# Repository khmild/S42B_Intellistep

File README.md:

# Intellistep

A rework of the terribly coded firmware from the BTT S42B v2 boards.

I am currently working on redoing a lot of the functions found in the firmware. A list of the current things that are being worked on is in the Projects tab. If you don't see your issue there, then please let me know.

***Note: This is a pre-release firmware still in beta testing. It is not ready for actual use yet. Only flash it if you would like to help with the development process. If you compile Intellistep and don't like it, you can always switch back to the production firmware using the file in the "precompiled" folder. The production firmware is `v2ProductionFirmware.bin`. Original BTT build of this project is `firmware-v2.0.bin`***

***Note: For the time being, all serial and CAN messages should start with "<" and end with ">". The serial baud rate is 115200.***

***Note: If you're having large oscillations in step correction, then try increasing the microstepping using the dip switches while increasing the microstep multiplier***

New Features:

- Redone stepping for higher torque and quieter operation
- Redone serial commands (based on gcode)
- Temperature readout on the display
- Motor and driver overtemp current reduction
- Much faster stepper calibration

Future Features:

- CAN subnetwork for driver configuration
- Dynamic current control based on speed and acceleration
- Manual tuning utility for manual PID tuning
- New menu items for setting PID parameters

G/M Code Table

- G6 (ex G6 D0 R1000 S1000) - Direct stepping, commands the motor to move a specified number of steps in the specified direction. D is direction (0 for CCW, 1 for CW), R is rate (in Hz), and S is the count of steps to move. Requires `ENABLE_DIRECT_STEPPING`
- M17 (ex M17) - Enables the motor (overrides enable pin)
- M18 / M84 (ex M18 or M84) - Disables the motor (overrides enable pin)
- M93 (ex M93 V1.8 or M93) - Sets the angle of a full step. This value should be 1.8° or 0.9°. If no value is provided, then the current value will be returned.
- M115 (ex M115) - Prints out firmware information, consisting of the version and any enabled features.
- M116 (ex M116 S1 M"A message") - Simple forward command that will forward a message across the CAN bus. Can be used for pinging or allowing a Serial to connect to the CAN network. Requires `ENABLE_CAN`
- M154 (ex M154 S8) - Runs the manual PID tuning interface. Serial is filled with encoder angles. S parameter specifies update interval in seconds. Requires `ENABLE_PID`
- M301 (ex M301 P1 I1 D1 W10 or M301) - Sets or gets the PID values for the motor. W term is the maximum value of the I windup. If no values are provided, then the current values will be returned. Requires `ENABLE_PID`
- M303 (ex M303) - Runs an autotune sequence for the PID loop. Requires `ENABLE_PID`
- M350 (ex M350 V16 or M350) - Sets or gets the microstepping divisor for the motor. This value can be 1, 2, 4, 8, 16, or 32. If no value is provided, then the current microstepping divisor will be returned.
- M352 (ex M352 S1 or M352) - Sets or gets the direction pin inversion for the motor (0 is standard, 1 is inverted). If no value is provided, then the current value will be returned.
- M353 (ex M353 S1 or M353) - Sets or gets the enable pin inversion for the motor (0 is standard, 1 is inverted). If no value is provided, then the current value will be returned.
- M354 (ex M354 S1 or M354) - Sets or gets if the motor dip switches were installed incorrectly (reversed) (0 is standard, 1 is inverted). If no value is provided, then the current value will be returned.
- M355 (ex M355 V1.34 or M355) - Sets or gets the microstep multiplier for the board. Allows to use multiple motors connected to the same mainboard pin, yet have different rates. If no value is provided, then the current value will be returned. Requires `ENABLE_CAN`
- M356 (ex M356 V1 or M356 VX2 or M356) - Sets or gets the CAN ID of the board. Can be set using the axis character or actual ID. If no value is provided, then the current value will be returned. Requires `ENABLE_CAN`
- M500 (ex M500) - Saves the currently loaded parameters into flash
- M501 (ex M501) - Loads all saved parameters from flash
- M502 (ex M502) - Wipes all parameters from flash, then reboots the system
- M907 (ex M907 R750, M907 I500) - Sets or gets the RMS(R) or Peak(P) current in mA. If dynamic current is enabled, then the accel(A), idle(I), and/or max(M) can be set or retrieved. If no value is set, then the current RMS current (not dynamic current) or the accel, idle, and max terms (dynamic current) will be returned.

Using dip switches
| Dip switch mappings
| PIN     |    Normal orientation      |  Reversed orientation |
|---------|----------------------------|-----------------------|
| DIP_1   |    Microstep 1             |  Calibration mode     |
| DIP_2   |    Microstep 2             |  Closed/Open loop     |
| DIP_3   |    Closed/Open loop        |  Microstep 2          |
| DIP_4   |    Calibration mode        |  Microstep 1          |

## Authors

## Credits

- [BTT](https://github.com/bigtreetech) - [Original code](https://github.com/bigtreetech/BIGTREETECH-Stepper-Motor-Driver)
- [CAP1Sup](https://github.com/CAP1Sup) - Main rewrite of code
- [IhorNehrutsa](https://github.com/IhorNehrutsa) - Large performance gains, general code work
- [TazerReloaded](https://github.com/TazerReloaded) - Encoder protocol and communication, much faster snprintf string printing
- [jlmxyz](https://github.com/jlmxyz) - Board schematics (in KiCad folder)
- [Misfittech](https://github.com/Misfittech) - The [Smart Stepper project](https://github.com/Misfittech/nano_stepper). This was a large help when writing the correct stepping code.
- [Matt Fryer](https://github.com/MattFryer) - [Smoothed](https://github.com/MattFryer/Smoothed) library. This was a huge help when smoothing out the OLED values to make them more readable and accurate
- [Marlin](https://github.com/MarlinFirmware/Marlin) - Autobuilding templates

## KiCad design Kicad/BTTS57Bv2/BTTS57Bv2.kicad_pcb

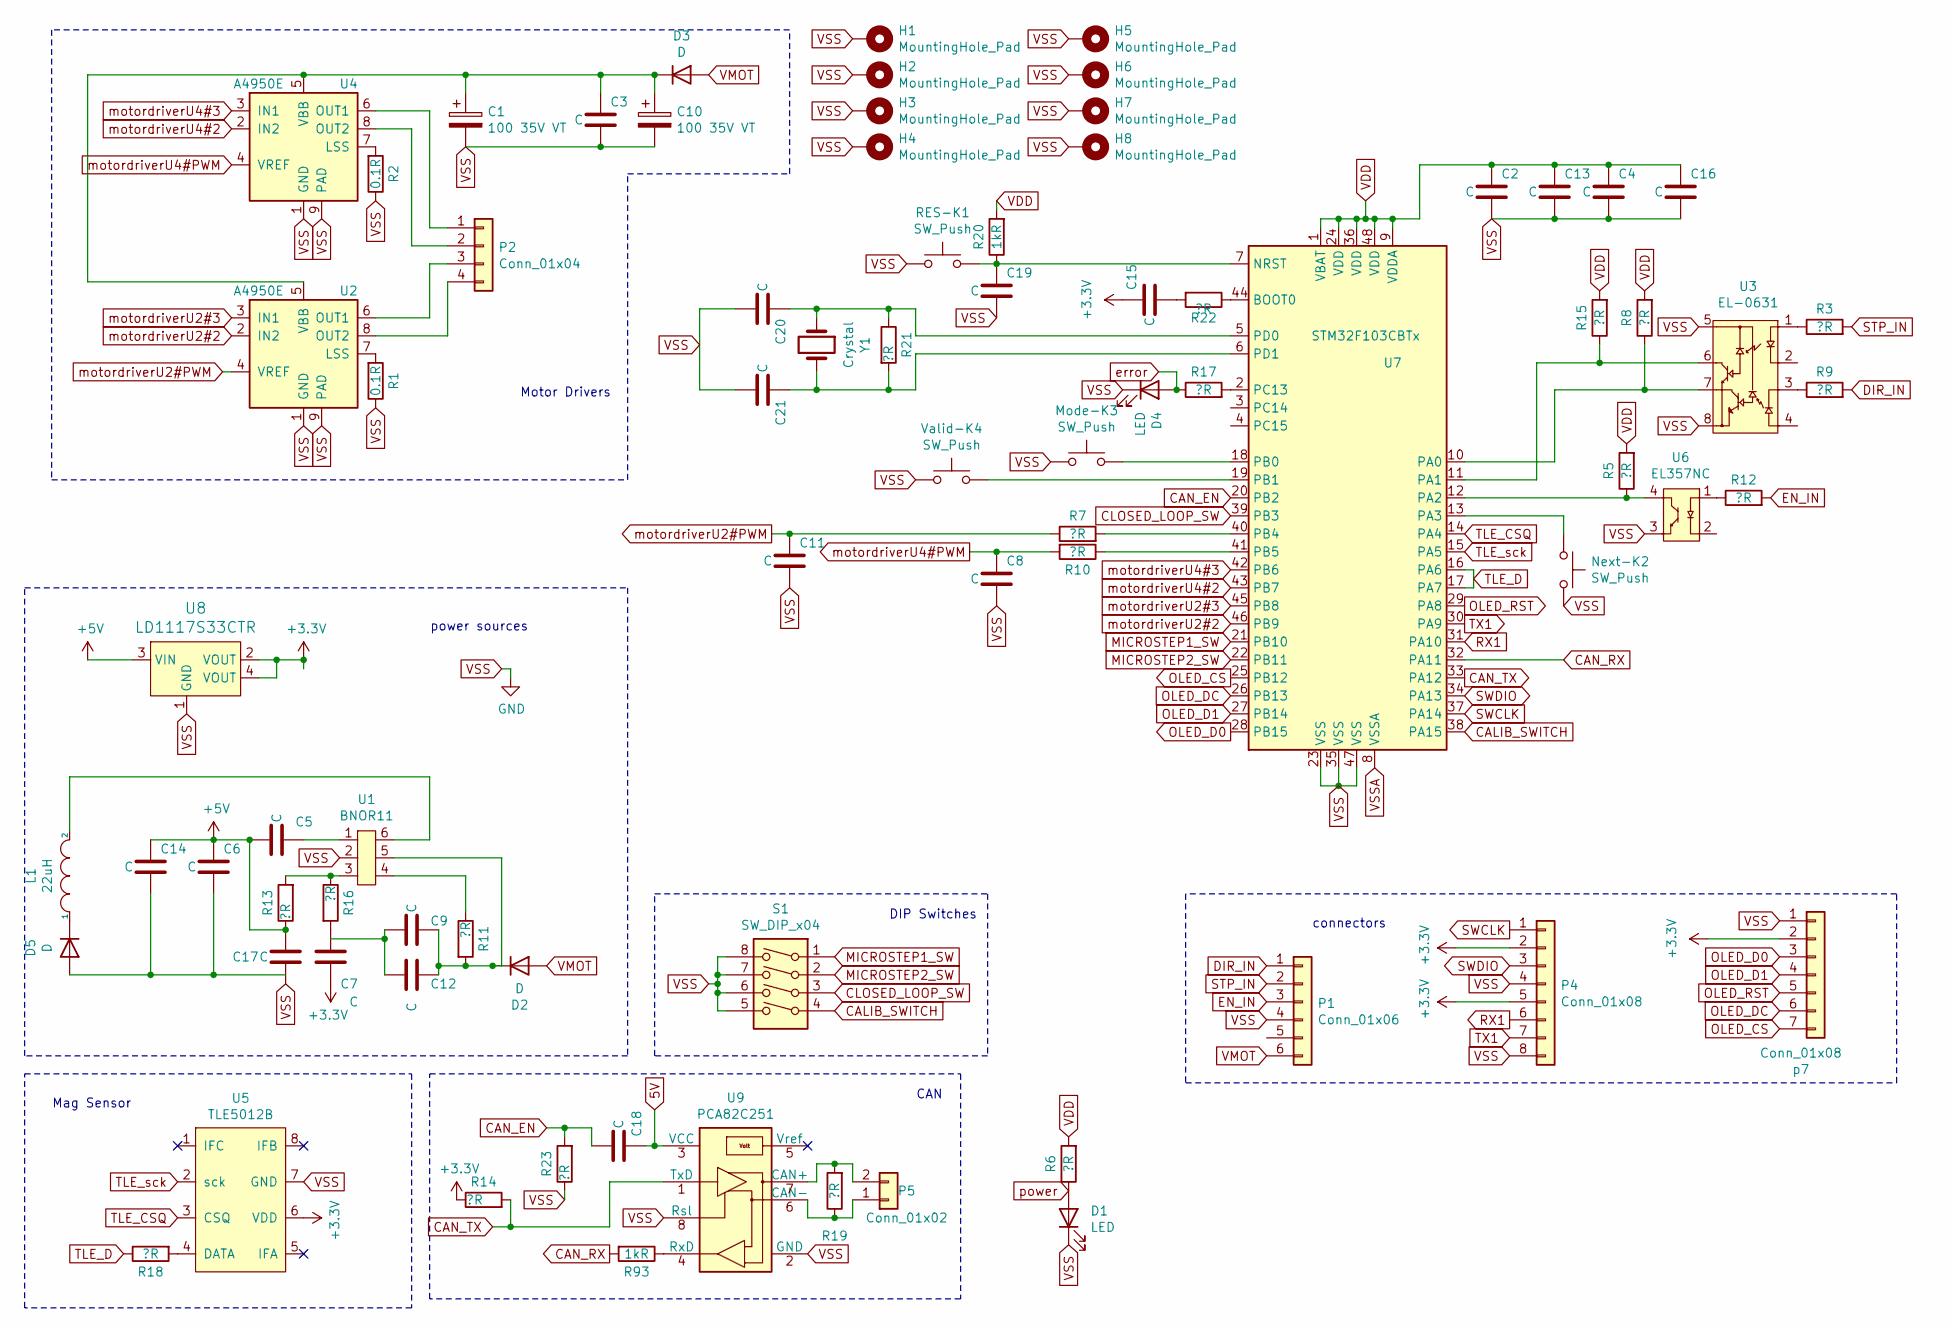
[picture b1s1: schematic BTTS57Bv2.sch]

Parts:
C1, C10: 100 35V VT; CP_Elec_6.3x7.7
C2, C4, C5, C8, C11, C12, C13, C14, C15, C16, C18, C19, C20, C21: C; C_0603_1608Metric
C3, C7, C17: C; C_1812_4532Metric
C6, C9: C; C_0805_2012Metric
D1, D4: LED; LED_0603_1608Metric
D2, D3, D5: D; D_2512_6332Metric
H1, H2, H3, H4, H5, H6, H7, H8: MountingHole_Pad; MountingHole_2.7mm_M2.5_ISO14580_Pad_TopBottom
L1: 22uH; L_Wuerth_MAPI-4030
Mode-K3: SW_Push; SW_Push_1P1T-SH_NO_CK_KMR2xxG
Next-K2: SW_Push; SW_Push_1P1T-SH_NO_CK_KMR2xxG
P1: Conn_01x06; JST_XH_B6B-XH-A_1x06_P2.50mm_Vertical
P2: Conn_01x04; JST_XH_B4B-XH-A_1x04_P2.50mm_Vertical
P4: Conn_01x08; PinHeader_1x08_P2.54mm_Vertical
P5: Conn_01x02; JST_XH_B2B-XH-AM_1x02_P2.50mm_Vertical
R1, R2: 0.1R; R_2512_6332Metric
R3, R9, R12, R18: ?R; R_0805_2012Metric
R5, R6, R7, R8, R10, R11, R13, R14, R15, R16, R17, R21, R22, R23: ?R; R_0603_1608Metric
R19: ?R; R_1206_3216Metric
R20, R93: 1kR; R_0603_1608Metric
RES-K1: SW_Push; SW_Push_1P1T-SH_NO_CK_KMR2xxG
S1: SW_DIP_x04; SW_DIP_SPSTx04_Slide_KingTek_DSHP04TS_W7.62mm_P1.27mm
U1: BNOR11
U2, U4: A4950E; SOIC-8-1EP_3.9x4.9mm_P1.27mm_EP2.41x3.3mm
U3: EL-0631; SOP-8_3.9x4.9mm_P1.27mm
U5: TLE5012B
U6: EL357NC; SOP-4_3.8x4.1mm_P2.54mm
U7: STM32F103CBTx; LQFP-48_7x7mm_P0.5mm
U8: LD1117S33CTR; SOT-223; MPN LD1117S33CTR; Digi-Key_PN 497-1241-1-ND
U9: PCA82C251; SO-8_3.9x4.9mm_P1.27mm
Valid-K4: SW_Push; SW_Push_1P1T-SH_NO_CK_KMR2xxG
Y1: Crystal
p7: Conn_01x08; PinSocket_1x07_P2.54mm_Vertical

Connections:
5V: C18.1, U9.3 (VCC)
+3V3: C7.2, C15.1, P4.2, P4.5, R14.1, U5.6 (VDD), U8.2 (VOUT), U8.4 (VOUT), p7.2
+5V: C5.2, C6.1, C14.1, C17.1, R13.1, U8.3 (VIN)
CALIB_SWITCH: S1.4, U7.38 (PA15)
CAN_EN: C18.2, R23.2, U7.20 (PB2)
CAN_RX: R93.2, U7.32 (PA11)
CAN_TX: R14.2, U7.33 (PA12), U9.1 (TxD)
CLOSED_LOOP_SW: S1.3, U7.39 (PB3)
DIR_IN: P1.1, R9.2
EN_IN: P1.3, R12.2
MICROSTEP1_SW: S1.1, U7.21 (PB10)
MICROSTEP2_SW: S1.2, U7.22 (PB11)
unnamed: C1.1, C3.1, C10.1, D3.1 (K), U2.5 (VBB), U4.5 (VBB)
unnamed: C5.1, U1.1
unnamed: C7.1, R16.2
unnamed: C9.1, C12.1, D2.1 (K), R11.2, U1.5
unnamed: C9.2, C12.2
unnamed: C6.2, C14.2, D5.2 (A)
unnamed: C15.2, R22.2
unnamed: C19.1, R20.1, RES-K1.2, U7.7 (NRST)
unnamed: C20.1, R21.1, U7.5 (PD0), Y1.1
unnamed: C21.1, R21.2, U7.6 (PD1), Y1.2
unnamed: D5.1 (K), L1.1
unnamed: L1.2, U1.6
unnamed: Mode-K3.2, U7.18 (PB0)
unnamed: Next-K2.1, U7.13 (PA3)
unnamed: P2.1, U4.6 (OUT1)
unnamed: P2.2, U4.8 (OUT2)
unnamed: P2.3, U2.6 (OUT1)
unnamed: P2.4, U2.8 (OUT2)
unnamed: P5.1, R19.1, U9.6 (CAN-)
unnamed: P5.2, R19.2, U9.7 (CAN+)
unnamed: R1.2, U2.7 (LSS)
unnamed: R2.2, U4.7 (LSS)
unnamed: R3.1, U3.1
unnamed: R5.1, U6.4, U7.12 (PA2)
unnamed: R7.2, U7.40 (PB4)
unnamed: R8.1, U3.7, U7.10 (PA0)
unnamed: R9.1, U3.3
unnamed: R10.1, U7.41 (PB5)
unnamed: R11.1, U1.4
unnamed: R12.1, U6.1
unnamed: R13.2, R16.1, U1.3
unnamed: R15.1, U3.6, U7.11 (PA1)
unnamed: R17.2, U7.2 (PC13)
unnamed: R18.2, U5.4 (DATA)
unnamed: R22.1, U7.44 (BOOT0)
unnamed: R93.1, U9.4 (RxD)
unnamed: U7.19 (PB1), Valid-K4.2
OLED_CS: U7.25 (PB12), p7.7
OLED_D0: U7.28 (PB15), p7.3
OLED_D1: U7.27 (PB14), p7.4
OLED_DC: U7.26 (PB13), p7.6
OLED_RST: U7.29 (PA8), p7.5
RX1: P4.6, U7.31 (PA10)
STP_IN: P1.2, R3.2
SWCLK: P4.1, U7.37 (PA14)
SWDIO: P4.3, U7.34 (PA13)
TLE_CSQ: U5.3 (CSQ), U7.14 (PA4)
TLE_D: R18.1, U7.16 (PA6), U7.17 (PA7)
TLE_sck: U5.2 (sck), U7.15 (PA5)
TX1: P4.7, U7.30 (PA9)
VDD: C2.1, C4.1, C13.1, C16.1, R5.2, R6.2, R8.2, R15.2, R20.2, U7.1 (VBAT), U7.9 (VDDA), U7.24 (VDD), U7.36 (VDD), U7.48 (VDD)
VMOT: D2.2 (A), D3.2 (A), P1.6
VSS: C1.2, C2.2, C3.2, C4.2, C8.2, C10.2, C11.2, C13.2, C16.2, C17.2, C19.2, C20.2, C21.2, D1.1 (K), D4.1 (K), H1.1, H2.1, H3.1, H4.1, H5.1, H6.1, H7.1, H8.1, Mode-K3.1, Next-K2.2, P1.4, P4.4, P4.8, R1.1, R2.1, R23.1, RES-K1.1, S1.5, S1.6, S1.7, S1.8, U1.2, U2.1 (GND), U2.9 (PAD), U3.5, U3.8, U4.1 (GND), U4.9 (PAD), U5.7 (GND), U6.3, U7.23 (VSS), U7.35 (VSS), U7.47 (VSS), U8.1 (GND), U9.2 (GND), U9.8 (Rsl), Valid-K4.1, p7.1
VSSA: U7.8 (VSSA)
error: D4.2 (A), R17.1
motordriverU2#2: U2.2 (IN2), U7.46 (PB9)
motordriverU2#3: U2.3 (IN1), U7.45 (PB8)
motordriverU2#PWM: C11.1, R7.1, U2.4 (VREF)
motordriverU4#2: U4.2 (IN2), U7.43 (PB7)
motordriverU4#3: U4.3 (IN1), U7.42 (PB6)
motordriverU4#PWM: C8.1, R10.2, U4.4 (VREF)
power: D1.2 (A), R6.1

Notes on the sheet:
power sources
Mag Sensor
CAN
DIP Switches
connectors
Motor Drivers

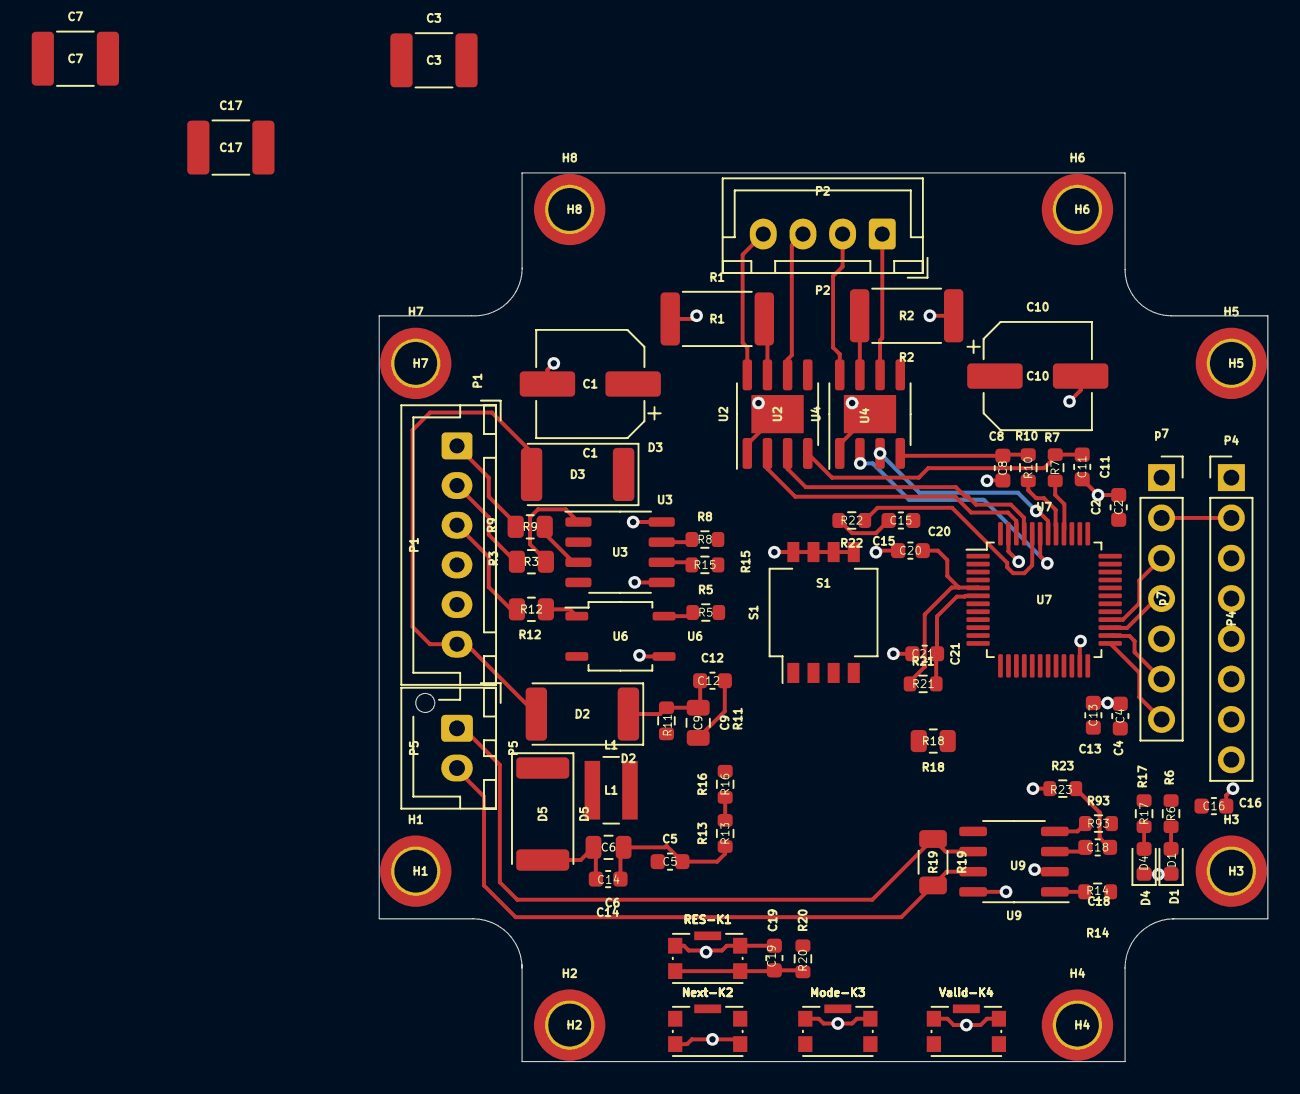
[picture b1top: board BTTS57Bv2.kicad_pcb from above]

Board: 2 copper layers, 56.0 x 56.0 mm, 74 parts (0 on the bottom side), 67 nets.

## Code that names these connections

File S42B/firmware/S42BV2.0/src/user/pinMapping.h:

#ifndef __PINMAPPING_H
#define __PINMAPPING_H

/*
// * = F103C8-CB    | DIGITAL | ANALOG | USART      | TWI       | SPI        | SPECIAL   |
//                  |---------|--------|------------|-----------|------------|-----------|
#define PA0  A0  // | 0       | A0     |            |           |            |           |
#define PA1  A1  // | 1       | A1     |            |           |            |           |
#define PA2  A2  // | 2       | A2     | USART2_TX  |           |            |           |
#define PA3  A3  // | 2       | A2     | USART2_RX  |           |            |           |
#define PA4  A4  // | 4       | A4     |            |           | SPI1_SS    |           |
#define PA5  A5  // | 5       | A5     |            |           | SPI1_SCK   |           |
#define PA6  A6  // | 6       | A6     |            |           | SPI1_MISO  |           |
#define PA7  A7  // | 7       | A7     |            |           | SPI1_MOSI  |           |
#define PA8  8   // | 8       |        |            |           |            |           |
#define PA9  9   // | 9       |        | USART1_TX  |           |            |           |
#define PA10 10  // | 10      |        | USART1_RX  |           |            |           |
#define PA11 11  // | 11      |        |            |           |            | USB_DN    |
#define PA12 12  // | 12      |        |            |           |            | USB_DP    |
#define PA13 13  // | 13      |        |            |           |            | SWD_SWDIO |
#define PA14 14  // | 14      |        |            |           |            | SWD_SWCLK |
#define PA15 15  // | 15      |        |            |           | SPI1_SS    |           |
//                  |---------|--------|------------|-----------|------------|-----------|
#define PB0  A8  // | 16      | A8     |            |           |            |           |
#define PB1  A9  // | 17      | A9     |            |           |            |           |
#define PB2  18  // | 18      |        |            |           |            | BOOT1     |
#define PB3  19  // | 19      |        |            |           | SPI1_SCK   |           |
#define PB4  20  // | 20      |        |            |           | SPI1_MISO  |           |
#define PB5  21  // | 21      |        |            |           | SPI1_MOSI  |           |
#define PB6  22  // | 22      |        | USART1_TX  | TWI1_SCL  |            |           |
#define PB7  23  // | 23      |        | USART1_RX  | TWI1_SDA  |            |           |
#define PB8  24  // | 24      |        |            | TWI1_SCL  |            |           |
#define PB9  25  // | 25      |        |            | TWI1_SDA  |            |           |
#define PB10 26  // | 26      |        | USART3_TX* | TWI2_SCL* |            |           |
#define PB11 27  // | 27      |        | USART3_RX* | TWI2_SDA* |            |           |
#define PB12 28  // | 28      |        |            |           | SPI2_SS*   |           |
#define PB13 29  // | 29      |        |            |           | SPI2_SCK*  |           |
#define PB14 30  // | 30      |        |            |           | SPI2_MISO* |           |
#define PB15 31  // | 31      |        |            |           | SPI2_MOSI* |           |
//                  |---------|--------|------------|-----------|------------|-----------|
#define PC13 32  // | 32      |        |            |           |            |           |
#define PC14 33  // | 33      |        |            |           |            | OSC32_IN  |
#define PC15 34  // | 34      |        |            |           |            | OSC32_OUT |
//                  |---------|--------|------------|-----------|------------|-----------|
#define PD0  35  // | 35      |        |            |           |            | OSC_IN    |
#define PD1  36  // | 36      |        |            |           |            | OSC_OUT   |
//                  |---------|--------|------------|-----------|------------|-----------|
*/

// OLED Mappings
#define OLED_CS_PIN   PB12
#define OLED_RST_PIN  PA8
#define OLED_SCLK_PIN PB13
#define OLED_SDIN_PIN PB14 // D1
#define OLED_DC_PIN   PB15 // ! Needs checked!
#define OLED_CS_GPIO_PORT  GPIOB
#define OLED_RST_GPIO_PORT GPIOB
#define OLED_DC_GPIO_PORT  GPIOB

// Button mappings
#define DOWN_BUTTON_PIN         PA3
#define BACK_BUTTON_PIN         PB0
#define SELECT_BUTTON_PIN       PB1

// Dip switch mappings
#define DIP_CALIBRATED          PA15
#define DIP_CLOSED_LOOP         PB3
#define DIP_MICRO_1             PB10
#define DIP_MICRO_2             PB11

// LED pin
#define LED_PIN PC13

// Motor mappings
#define COIL_A_DIR_1        PB6
#define COIL_A_DIR_2        PB7
#define COIL_B_DIR_1        PB8
#define COIL_B_DIR_2        PB9
#define COIL_A_POWER_OUTPUT PB4
#define COIL_B_POWER_OUTPUT PB5

// Encoder SPI interface
#define ENCODER_SS   PA4 // SPI1_SS
#define ENCODER_SCK  PA5 // SPI1_SCK
#define ENCODER_MISO PA6 // SPI1_MISO
#define ENCODER_MOSI PA7 // SPI1_MOSI

// Stepping interface
#define STEP_PIN      PA1 // ! according to the previous files, but this is the same as the dir pin
#define ENABLE_PIN    PA2
#define DIRECTION_PIN PA1

// CAN bus pins
#define CAN_IN_PIN  PA11
#define CAN_OUT_PIN PA12



// Options
#define CLOSED_LOOP
#define CLOSED_LOOP_CONFIG
//#define TEST_FLASH
#define STEPPER_UPDATE_FREQ 10

// Encoder speed estimation instead of actual value (saves memory)
//#define ENCODER_ESTIMATION

// Motor constants
#define STEP_ANGLE 1.8 // ! Check to see for .9 deg motors as well
#define MAX_CURRENT 3500 // Maximum current in mA
#define MAX_MICROSTEP_DIVISOR 32 // The maximum microstepping divisor

#endif //__PINMAPPING_H

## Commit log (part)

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2021-02-15 Wrote motor groundwork, reintroduced flash, and continued work on menu display
2021-02-19 Added serial interface (needs parser), added loading saved values
2021-02-21 Fixed some minor issues with the parser
2021-02-23 Added TLE5012 library, needs implementation
2021-02-23 Fixed compilation error
2021-02-23 Added command to save parameters to flash, more parser work
2021-02-24 Added microstepping menu, needs enable and direction menus
2021-02-25 Moved parser to seperate file in prep for CAN reimplementation
2021-02-28 Added hardware timers with IRQ for stepper
2021-02-28 Fixed README and minor stepping speed issue
2021-02-28 Added datasheets for components
2021-03-01 Fixed serial reads
2021-03-01 Updated warning to README and added quick call to parse the serial data
2021-03-01 Updated README with serial baud
2021-03-02 Added debugging print
2021-03-04 Changed motor operation to only use PID for corrections
2021-03-19 Fixed issues with firmware lock (caused by encoder). Menu system is almost fully functional
2021-03-20 Fixed include error from c_cpp_properties.json
2021-03-30 Redid the stepper coil calculations with help from Misfittech. Note that this still needs testing
2021-03-30 Fixed coding issue with motor class and added blank menu item before wraparound
2021-03-31 Added step correction (not enabled, needs encoder yet)
2021-04-03 Added microstep multiplier (request of @maracMB)
2021-04-03 Moved encoder back to library, no values yet
2021-04-05 Bypassed booting issue, added debug print. Encoder still not working
2021-04-06 Fixed logic issues with stepping timers. Needs second lookover
2021-04-06 Redid timers and stepping method. Added StallFault detection.
2021-04-06 Added option to StallFault based on angle deviation
2021-04-08 Moved to manual encoder SPI config. Not working yet
2021-04-09 Roughly fixed delays, tried to fix encoder issue, no luck
2021-04-11 Encoder values are here! Just stepping left. Thanks to TazerReloaded for the fix
2021-04-11 Added speed estimation, fixed temp and angle values
2021-04-11 Fixed readMultipleEncoderRegisters removed some debug statements
2021-04-13 Fixed sine coil calculations, added script to generate table
2021-04-14 Massively improved OLED code and much higher speeds
    OLED code was commented and redone for readability. Screen buffer is written only when needed
2021-04-15 Fixed enabling and current calculations. Stepping still needs work
2021-04-20 OLED cleanup, motor function consolidation, bootscreen
    Also added versioning and gcode for firmware info
2021-04-29 Added feature selection and firmware feature print
2021-04-30 Added exclusion for 0 current for motor.
    Should fix issues with extra current draw.
2021-05-06 Found issue with stepping. Added stepping (only for debugging), disabled CAN
    Issue was caused by CAN bus trying to use the same pins. The CAN library needs a minor rewrite
2021-05-06 Added encoder absolute angle and offset calibration, needs testing
2021-05-07 Added encoder zeroing
2021-05-10 Issues with encoder revolutions should be fixed
    Needs testing. Manually set bits instead of using the TLE library's version
2021-05-10 Still have encoder issues with revolutions, library issues
    Rewrite of library is broken. All of OLED is now cleared after the motor data.
2021-05-11 MovingAverage library fixed, speed gains are evident
2021-05-11 Added OLED renaming, needs testing
2021-05-12 Added autobuilding configs, removed old define
2021-05-12 Fixed filenaming issue with autobuilding
2021-05-13 Fixed minor issues were display was not updating
2021-05-13 Autobuilding should be fixed
2021-05-13 Removed old autobuild file
2021-05-13 Added Marlin credit
2021-05-17 Display warning implementation
2021-05-18 Minor addition to set current to deal with loopback
2021-05-19 Fixed OLED call for speed estimation
2021-05-20 Changed RPM to 2 decimal places
2021-05-20 Improved output for unstable numbers
2021-06-05 reverse engeenering v0.1.0 - need verification : - CAN_EN - double checks all non MCU connected signals - clock generation
2021-06-07 added footprint information changed orientation of oled connector added mounting holes PCB reverse creation (high parts are positionned according measurements, same for outline)
2021-06-09 Fixed 2 minor issues with step correction
2021-06-13 Fixed forced enable issue, began flash rework, added returns to blank commands
    Flash isn't ready yet, but soon. Also fixed issues with correction timer not being reset correctly
2021-06-15 Fixed minor issue causing build to fail with dynamic current
2021-06-16 Fixed minor logic error with stepping IRQ
2021-06-17 Save a little time in fastSin() and fastCos()
    Use SINE_VAL_COUNT as a power of 2.
2021-06-17 Flash works properly now
    Re-enabled calibration check (still doesn't do anything) and added message at boot
2021-06-17 Added M115 support for overtemp and restructured M115 print
2021-06-17 Added OLED parameter saving, loading, and wiping
    Also redid some of the OLED prints to be based on a #defined line height
2021-06-18 Cleanup fastSine.h
2021-06-18 revert
2021-06-20 Added temporary fix for motor calibration issues
    Also fixed unwanted back button behavior on calibration prompt
2021-06-22 Create main_formatted.c
    Save main.c as main_formatted.c and format it in VisualCode
2021-06-23 Revert motor.cpp
2021-06-23 Revert main.cpp
2021-06-23 Fixed issue with SYSCLK selection
2021-06-23 Fixed missed setCoil lines
2021-06-24 StallFault should be working with LED (not tested or enabled)
2021-06-24 Added Klipper files
    Completely unorganized, unworking, and probably going to fail when building
2021-06-24 Add Cube project
2021-06-24 Fixed issues with remaining flash PID references
2021-06-26 Added DS_Store to git ignore
2021-06-28 speedup
2021-06-29 Fixed issues with direction pins not being intialized
2021-06-29 CHECK_GPIO_OUTPUT_SWITCHING
2021-06-29 Fixed motor PWM freq and version number
    In response to https://github.com/CAP1Sup/Intellistep/issues/39
2021-06-30 Update flash.cpp
    Fix #41
2021-06-30 Update main.cpp
    while formatting
2021-06-30 Update timers.cpp
    Add CHECK_STEPPING_RATE funtionality
2021-06-30 Remove unused 'direction' parametr from driveCoils()
2021-06-30 Use separate previousCoilState's for motor coils
2021-06-30 StepperMotor::simpleStep() for tests
2021-06-30 Enable all compiler warnings
2021-06-30 Added parenthesis, modified how steps are calculated
2021-06-30 Cleanup of files, moved all calls to use GPIO_READ
2021-06-30 Added PID warning in preparation to merge with master
2021-07-01 StepperMotor.reversed must be signed type
2021-07-02 SINE_MAX a power of 2 to fast division to SINE_MAX
2021-07-02 Use uint16_t in analogSet() and analogSetup()
2021-07-02 Performance curves of stepper motor on page 2
2021-07-02 Added better notes, minor changes
    SINE_POWER is automatically computed during build, fixed PWM uint16_ts
2021-07-02 Moved SINE_MAX sanity checks to their respective file
2021-07-02 Added note on FALLING step pin
2021-07-05 128MHz overclock
2021-07-06 Measure PLLCLK on MCO(PA8)
2021-07-06 Fixed the previous coil state so that it is set at boot
2021-07-06 Rewrote PID, added tuner project, added I windup limit
    PID should be fully functional.
2021-07-07 Re-enabled the startup offset and moved flash program to IRQ
2021-07-07 Added direct stepping
    Also changed around parser to support DS and added timer
2021-07-07 Fixed missing reference due to encoder class creation
2021-07-08 Reduce motor noise: Set MOTOR_PWM_FREQ to 140kHz
    140kHz measured in origin BTT board.
    See https://github.com/CAP1Sup/Intellistep/issues/39
2021-07-08 Moved PWM settings to config
2021-07-08 Set motor PWM 139.5kHz and 9bit resolution
2021-07-09 Split getAngle() to getAngleNow() and getAngleAvg()
2021-07-09 Check encoder speed
2021-07-09 Remove the LGPL comment as inaccurate
2021-07-09 Init running total to zero
2021-07-09 Reduce code size
2021-07-09 Use integer MovingAverage to encoder Angle funcctions
2021-07-11 First try at DMA transfer, no luck so far
    Transfer complete function doesn't seem to be called
2021-07-12 Serial.setTx() Serial.setRx()
2021-07-12 Code review of Encoder Temperature
2021-07-12 Cleaned up config.h
2021-07-13 Added credit for board schematics
2021-07-13 Replace pow() function to constant macro
2021-07-13 Cleaned up config.h, moved most macros to macros.h
    Should help to keep the config clean for when people configure it
2021-07-13 Fix !ENCODER_SPEED_ESTIMATION
2021-07-14 Hardware step counter
    Steps are also counted by a separate hardware counter, allowing higher precision. Needs over/underflow interrupts
2021-07-14 Minor changes, new debugging section, flash version ignore
    Also cleaned up getRev and made it an integer
2021-07-14 Fix Encoder::getTemp()
2021-07-15 Finished hardware counter
    PID now uses the hardware counter as its reference
2021-07-15 Added enable pin config (accidentally removed)
2021-07-15 Fix microstepMultiplier
2021-07-15 5.6 hour in one direction for counter overflow
2021-07-16 Use momentary values of encoder with rejected LSB
2021-07-17 Clarification and cleanup
    Moved config into separate files, streamlining process for end users
2021-07-17 Renamed encoder function, reorganized configs
    Configs are now in a separate folder, making it easier to keep configs separate from coded files
2021-07-17 Minor conventions cleanup
2021-07-17 Fixed version and minor issue with hardware step count
2021-07-19 Started work on enabling issue, not finished yet
2021-07-19 Use indexPointsMultiplier
2021-07-27 Cleanup of unneeded additions and calculations
    Angles are no longer calculated, they can be found by multipling the current step count by the microstepAngle
2021-07-28 Select only step/dir mode
2021-08-03 Fixes to setState
    Set state should now work properly
2021-08-03 Fixed minor issue with ambigous call
2021-08-04 Remove CLOCKWISE and COUNTER_CLOCKWISE
2021-08-05 Use POSITIVE/NEGATIVE
2021-08-06 Use momentary encoder.getAbsoluteAngle()
2021-08-08 bug fix : wrong pin count order on optical tranceivers
2021-08-10 private microstepMultiplier
2021-08-11 Zero the encoder after the motor is enabled
2021-08-11 delay(500)
2021-08-13 Fix software counter direction
2021-08-13 Merge remote-tracking branch 'origin/dev' into RevIngSchematics
    # Conflicts:
    # .gitignore
    # Kicad/BTTS42Bv2/BTTS42Bv2-cache.lib
    # Kicad/BTTS42Bv2/BTTS42Bv2.sch
    # Kicad/BTTS42Bv2/BTT_S57B_v2.0_reverseIng.0.1.1.pdf
2021-08-13 renaming folder name
2021-08-14 Set priority groupping explicitly to 3.1(PRIO.SUBPRIO)
2021-09-02 Fixed issues with saving that cause encoder output to be "nan"
    Should fix https://github.com/CAP1Sup/Intellistep/issues/107
2021-11-21 Hardware counting improvements
    Motor setup now uses STM library. Minor miscounting does occasionally occur, causing drifts of around 1-2 steps, but these occur rarely. More work needs done yet. Also added feature to display step c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
2021-11-27 Minor commenting adjustment, makes objective clearer
2021-11-28 Added optimized function for much faster GPIO7 writes
    Improves encoder read and write speeds. Also fixed version number
2021-11-29 Added legacy step code and option to switch between
    Another attempt at #111. No luck still
2021-12-02 Added nice cycling animation to calibration messages
2021-12-10 Added enable pin interrupt support
    This is disabled as the functionality is untested
2021-12-10 Added preprocessor statement to scrolling logic
    Fixes extra unnecessary variables when OLED isn't enabled
2021-12-11 Fixed motor not disabling (PULLDOWN -> PULLUP)
2021-12-12 Added MKS step counting. Original encoder setup better
2022-01-29 Default to no overclock, flash load optimization
2022-01-29 Minor adjustment to README
2022-02-08 Adjusted warning message, needs testing
2022-07-21 motor eable bug fixed, pid works after stepping
2022-07-24 runout after G6 fixed
2022-08-08 Motor in position indication
2022-09-08 acceleration functions added
2022-11-14 new pid process
2022-12-30 stallfault removed
2022-12-30 stepping velocity removed
2023-01-19 s_curve acceleration with position regulation
2023-02-10 code cleanup(working wersion)
